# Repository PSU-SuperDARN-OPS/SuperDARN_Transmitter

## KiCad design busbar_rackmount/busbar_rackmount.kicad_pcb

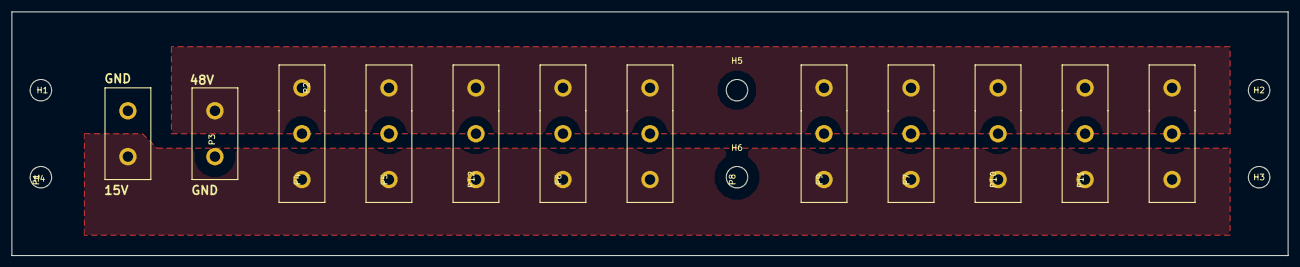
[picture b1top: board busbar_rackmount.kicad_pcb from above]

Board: 2 copper layers, 220.0 x 42.0 mm, 18 parts (0 on the bottom side), 3 nets, no tracks yet.

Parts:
H1, H2, H3, H4, H5, H6: MOUNTING_HOLE; MountingHole_3-7mm
P1, P2: CONN_01X02; powerpole25APCBx2
P3, P4, P5, P6, P7, P8, P9, P10, P11, P12: CONN_01X03; powerpole25APCBx3

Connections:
+15V: P1.1, P3.1, P4.1, P5.1, P6.1, P7.1, P8.1, P9.1, P10.1, P11.1, P12.1
+48V: P2.1, P3.3, P4.3, P5.3, P6.3, P7.3, P8.3, P9.3, P10.3, P11.3, P12.3
GND: P1.2, P2.2, P3.2, P4.2, P5.2, P6.2, P7.2, P8.2, P9.2, P10.2, P11.2, P12.2

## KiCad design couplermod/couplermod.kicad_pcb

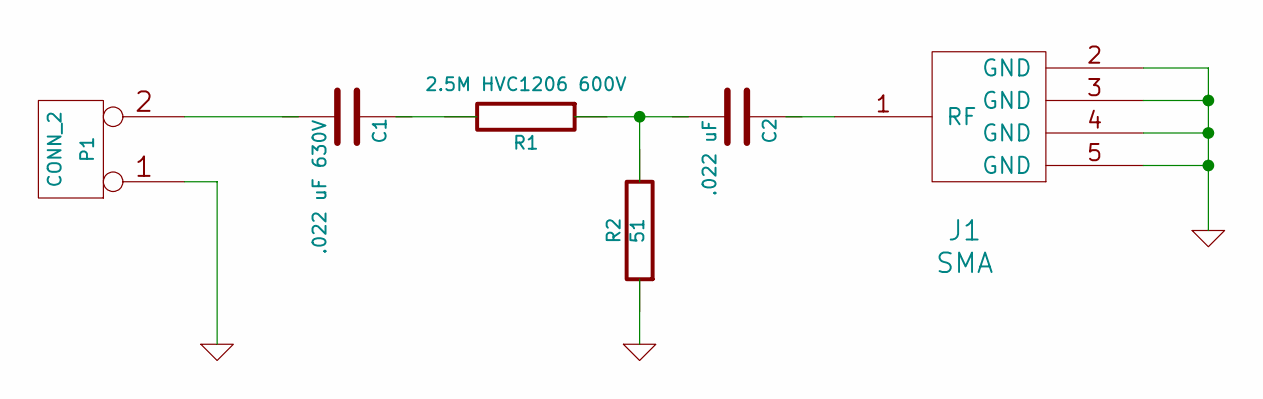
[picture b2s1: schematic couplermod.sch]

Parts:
C1: .022 uF 630V; SMD-1210
C2: .022 uF; SMD-1210
J1: SMA; sma
P1: CONN_2; SIL-2
R1: 2.5M HVC1206 600V; SMD-1210
R2: 51; SMD-0805

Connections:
GND: J1.2 (GND), J1.3 (GND), J1.4 (GND), J1.5 (GND), P1.1, R2.1
unnamed: C1.1, R1.2
unnamed: C1.2, P1.2 (PM)
unnamed: C2.1, J1.1 (RF)
unnamed: C2.2, R1.1, R2.2

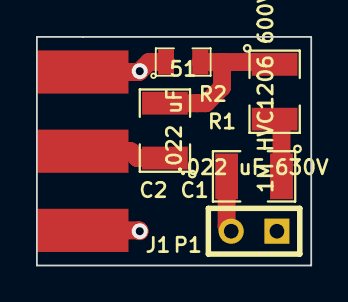
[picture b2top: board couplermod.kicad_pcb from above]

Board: 2 copper layers, 15.2 x 12.7 mm, 6 parts (0 on the bottom side), 5 nets.

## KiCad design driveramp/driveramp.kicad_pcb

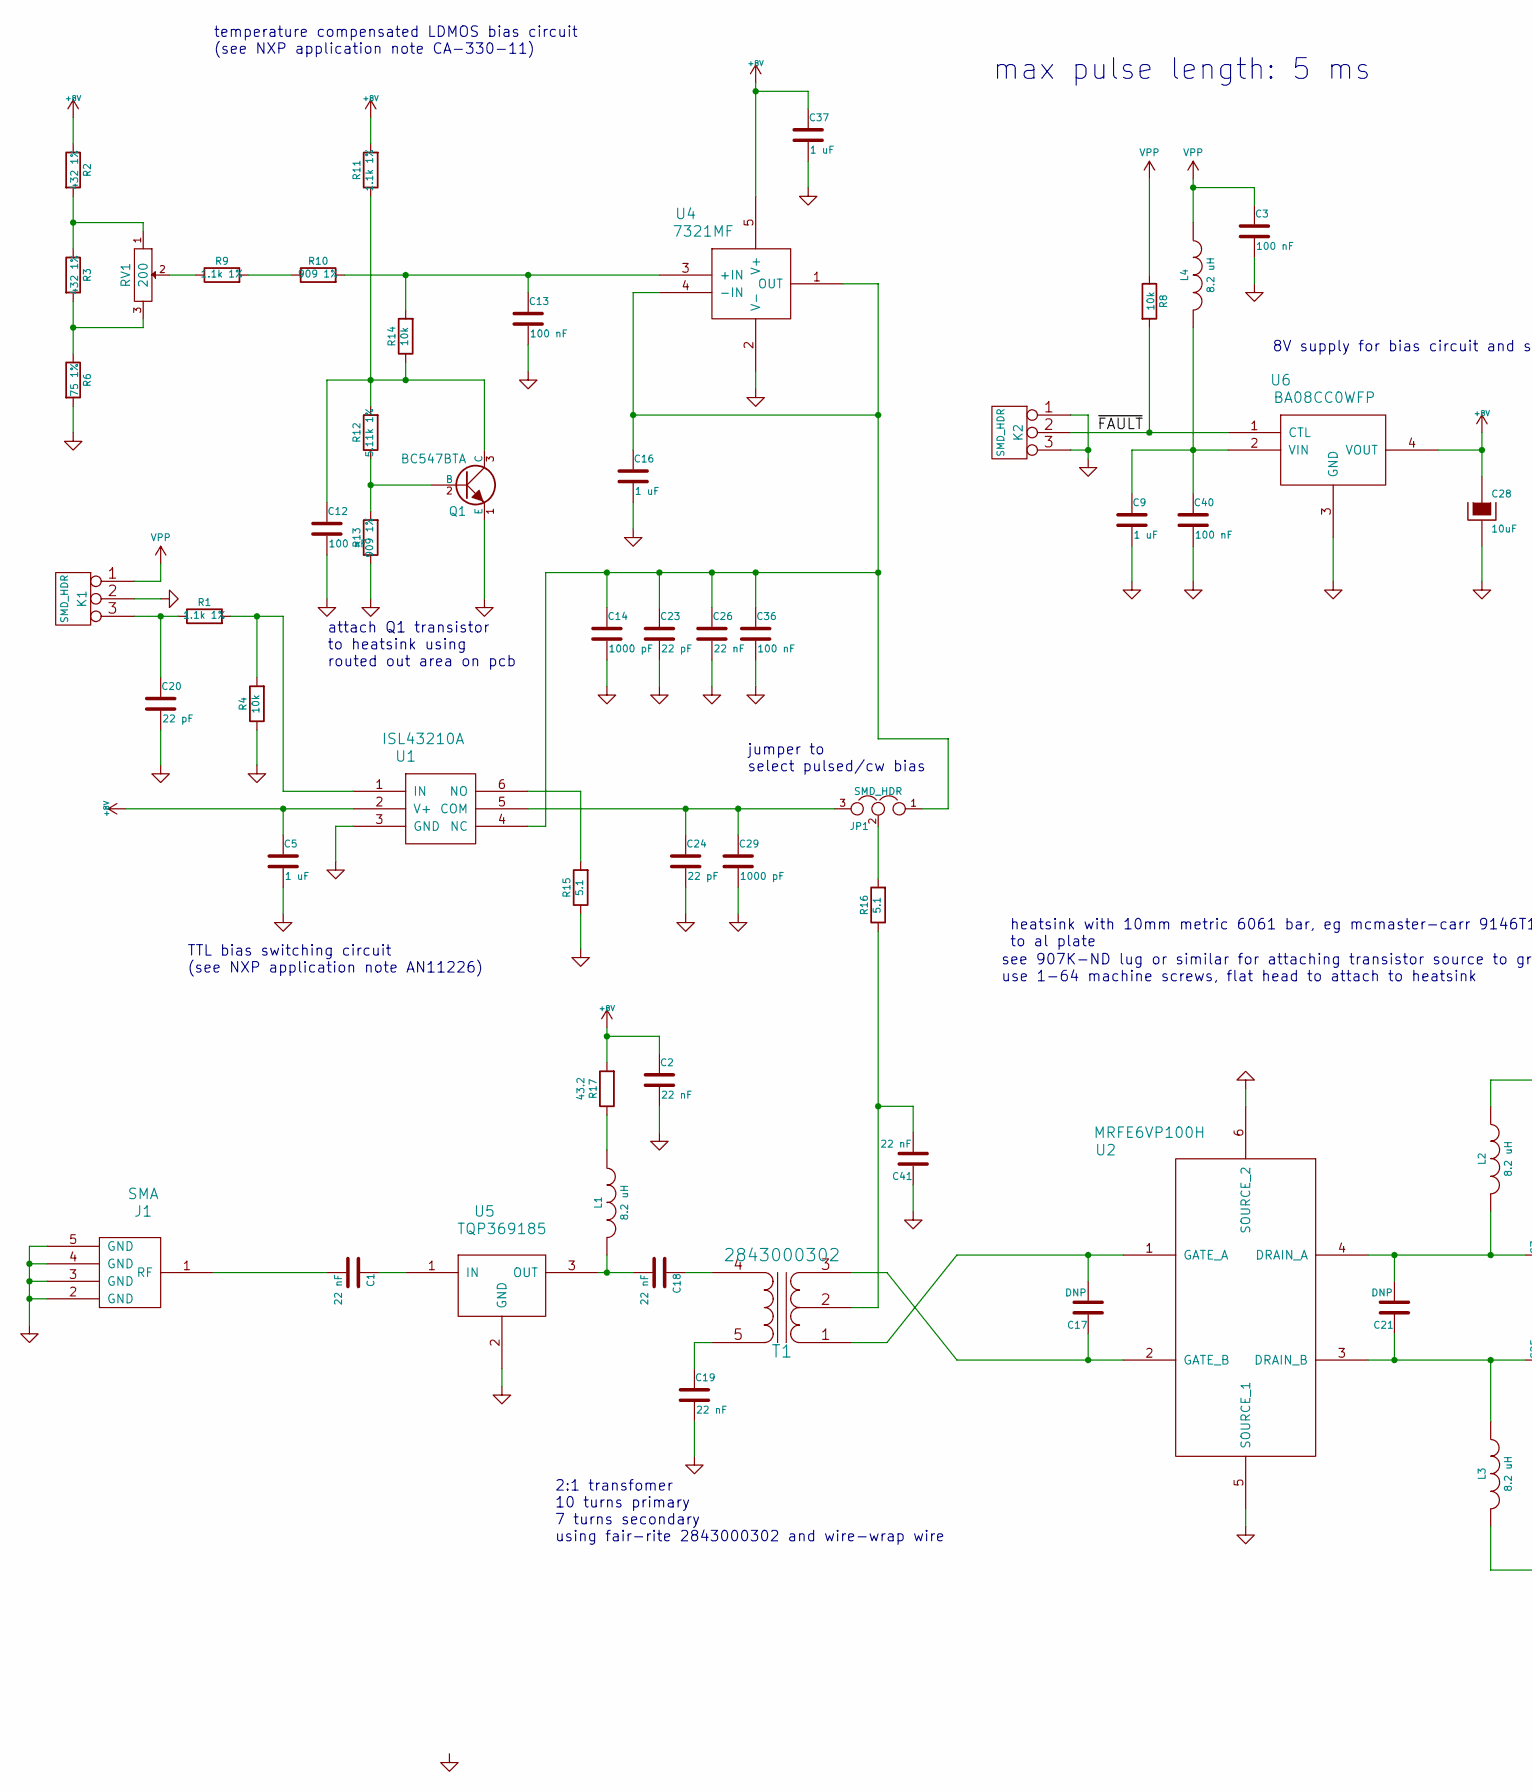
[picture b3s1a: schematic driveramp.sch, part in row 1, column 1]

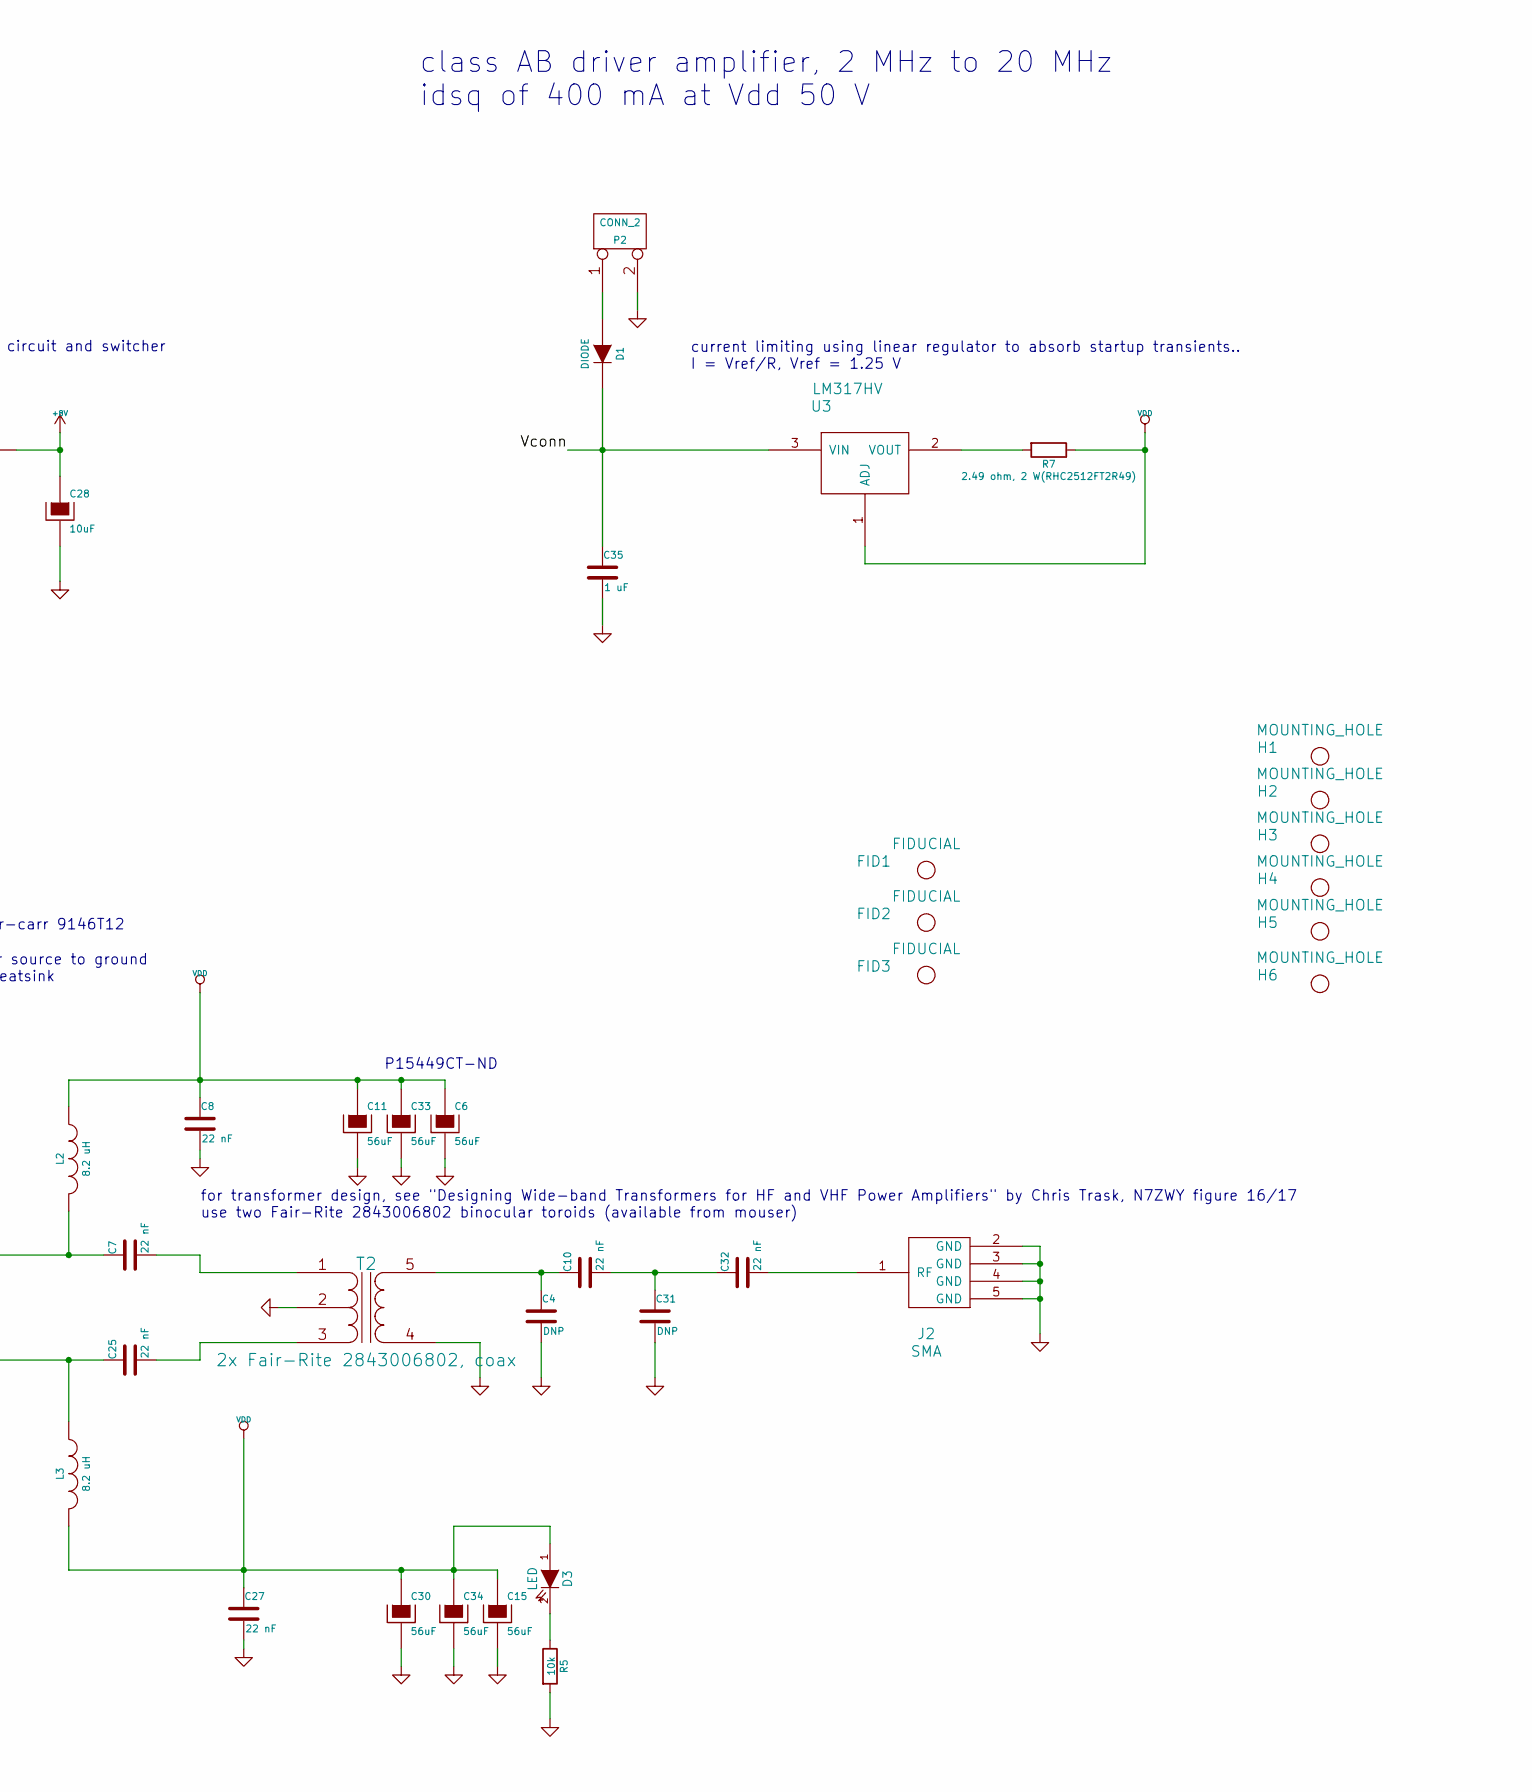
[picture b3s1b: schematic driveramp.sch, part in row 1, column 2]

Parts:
C1, C2, C7, C8, C10, C18, C19, C25, C26, C27, C32, C41: 22 nF; SMD-0805; MFG PN GRM21BR72A223KA01L
C3, C12, C13, C36, C40: 100 nF; SMD-0805; MFG PN CL21B104KCC5PNC
C4, C31: DNP; SMD-1210
C5, C9, C16, C35, C37: 1 uF; C_0805; MFG PN CGA4J3X7S2A105K125AE
C6, C11, C15, C30, C33, C34: 56uF; c_elec_10x10; MFG PN EEH-ZA1J560P
C14, C29: 1000 pF; SMD-0805; MFG PN GRM2195C2A102JA01D
C17, C21: DNP; SMD-0805
C20, C23, C24: 22 pF; C_0805; MFG PN CL21C220JCANNNC
C28: 10uF; c_1210; MFG PN TAJB106M020RNJ
D1: DIODE; DO-214-AA_SMB; MFG PN ES2B
D3: LED; LED-0805; MFG PN LS R976-NR-1
FID1, FID2, FID3: FIDUCIAL; FID_1MM
H1, H2, H3, H4: MOUNTING_HOLE; MountingHole_3-5mm
H5, H6: MOUNTING_HOLE; MountingHole_2-7mm
J1, J2: SMA; SMA_0732511350; MFG PN 732511350
JP1: SMD_HDR; 0740991003
K1, K2: SMD_HDR; 0740991003; MFG PN 740991003
L1, L2, L3, L4: 8.2 uH; Choke_SMD_Wuerth-WE-PD2-Typ-L; MFG PN 7447786008
P2: CONN_2; 2-1445053-2; MFG PN 2-1445096-2
Q1: BC547BTA; TO92SMDSENSE; MFG PN BC547BTA
R1, R9, R11: 1.1k 1%; R_0603; MFG PN ERJ-3EKF1101V
R2, R3: 432 1%; R_0603; MFG PN ERJ-3EKF4320V
R4, R5, R8, R14: 10k; R_0603; MFG PN ERJ-3EKF1002V
R6: 75 1%; R_0603; MFG PN ERJ-3EKF75R0V
R7: 2.49 ohm, 2 W(RHC2512FT2R49); SM2512; MFG PN RHC2512FT2R49
R10, R13: 909 1%; R_0603; MFG PN ERJ-3EKF9090V
R12: 5.11k 1%; R_0603; MFG PN ERJ-3EKF5111V
R15, R16: 5.1; R_0603; MFG PN ERJ-3EKF5111V
R17: 43.2; SMD-2512_Pol; MFG PN MCR100JZHF43R2
RV1: 200; 3269W; MFG PN 3269W-1-201GLF
T1: 2843000302; MFG PN 2843000302
T2: 2x Fair-Rite 2843006802, coax; 2843006802; MFG PN 2843006802
U1: ISL43210A; SOT-23-6; MFG PN ISL43210AIHZ-T7A
U2: MRFE6VP100H; NI780-4; MFG PN MRFE6VP100HR5
U3: LM317HV; TO-220_Neutral123_Horizontal; MFG PN LM317HVT/NOPB
U4: 7321MF; SOT-23-5; MFG PN LM7321MF/NOPB
U5: TQP369185; SOT89-3_Housing; MFG PN TQP369185
U6: BA08CC0WFP; TO252-5; MFG PN BA08CC0WFP-E2

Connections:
+8V: C2.1, C5.1, C28.1, C37.1, R2.1, R11.2, R17.2, U1.2 (V+), U4.5 (V+), U6.4 (VOUT)
/Vconn: C35.1, D1.2 (K), U3.3 (VIN)
/~FAULT: K2.2 (PM), R8.2, U6.1 (CTL)
GND: C2.2, C3.2, C4.2, C5.2, C6.2, C8.2, C9.2, C11.2, C12.2, C13.2, C14.2, C15.2, C16.2, C19.2, C20.2, C23.2, C24.2, C26.2, C27.2, C28.2, C29.2, C30.2, C31.2, C33.2, C34.2, C35.2, C36.2, C37.2, C40.2, C41.1, J1.2 (GND), J1.3 (GND), J1.4 (GND), J1.5 (GND), J2.2 (GND), J2.3 (GND), J2.4 (GND), J2.5 (GND), K1.2 (PM), K2.1, K2.3, P2.2 (PM), Q1.1 (E), R4.1, R5.2, R6.2, R13.1, R15.1, T2.2 (PM), T2.4 (S1), U1.3 (GND), U2.5 (SOURCE_1), U2.6 (SOURCE_2), U4.2 (V-), U5.2 (GND), U6.3 (GND)
unnamed: C1.1, U5.1 (IN)
unnamed: C1.2, J1.1 (RF)
unnamed: C7.2, T2.1 (PR1)
unnamed: C4.1, C10.1, T2.5 (S2)
unnamed: C10.2, C31.1, C32.1
unnamed: C12.1, Q1.3 (C), R11.1, R12.2, R14.1
unnamed: C13.1, R10.2, R14.2, U4.3 (+IN)
unnamed: C14.1, C16.1, C23.1, C26.1, C36.1, JP1.1, U1.4 (NC), U4.1 (OUT), U4.4 (-IN)
unnamed: C17.1, T1.3 (PR2), U2.2 (GATE_B)
unnamed: C17.2, T1.1 (PR1), U2.1 (GATE_A)
unnamed: C18.1, T1.4 (S1)
unnamed: C18.2, L1.2, U5.3 (OUT)
unnamed: C19.1, T1.5 (S2)
unnamed: C20.1, K1.3, R1.1
unnamed: C21.1, C25.1, L3.1, U2.3 (DRAIN_B)
unnamed: C7.1, C21.2, L2.2, U2.4 (DRAIN_A)
unnamed: C24.1, C29.1, JP1.3, U1.5 (COM)
unnamed: C25.2, T2.3 (PR2)
unnamed: C32.2, J2.1 (RF)
unnamed: C9.1, C40.1, L4.2, U6.2 (VIN)
unnamed: C41.2, R16.1, T1.2 (PM)
unnamed: D1.1 (A), P2.1
unnamed: D3.2 (K), R5.1
unnamed: JP1.2, R16.2
unnamed: L1.1, R17.1
unnamed: Q1.2 (B), R12.1, R13.2
unnamed: R1.2, R4.2, U1.1 (IN)
unnamed: R2.2, R3.1, RV1.1
unnamed: R3.2, R6.1, RV1.3
unnamed: R7.2, U3.2 (VOUT)
unnamed: R9.1, RV1.2
unnamed: R9.2, R10.1
unnamed: R15.2, U1.6 (NO)
VDD: C6.1, C8.1, C11.1, C15.1, C27.1, C30.1, C33.1, C34.1, D3.1 (A), L2.1, L3.2, R7.1, U3.1 (ADJ)
VPP: C3.1, K1.1, L4.1, R8.1

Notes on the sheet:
class AB driver amplifier, 2 MHz to 20 MHz idsq of 400 mA at Vdd 50 V
P15449CT-ND
for transformer design, see "Designing Wide-band Transformers for HF and VHF Power Amplifiers" by Chris Trask, N7ZWY figure 16/17 use two Fair-Rite 2843006802 binocular toroids (available from mouser)
current limiting using linear regulator to absorb startup transients.. I = Vref/R, Vref = 1.25 V
max pulse length: 5 ms
see 907K-ND lug or similar for attaching transistor source to ground use 1-64 machine screws, flat head to attach to heatsink
temperature compensated LDMOS bias circuit (see NXP application note CA-330-11)
TTL bias switching circuit (see NXP application note AN11226)
8V supply for bias circuit and switcher
heatsink with 10mm metric 6061 bar, eg mcmaster-carr 9146T12 to al plate
attach Q1 transistor to heatsink using routed out area on pcb
jumper to select pulsed/cw bias
2:1 transfomer 10 turns primary 7 turns secondary using fair-rite 2843000302 and wire-wrap wire

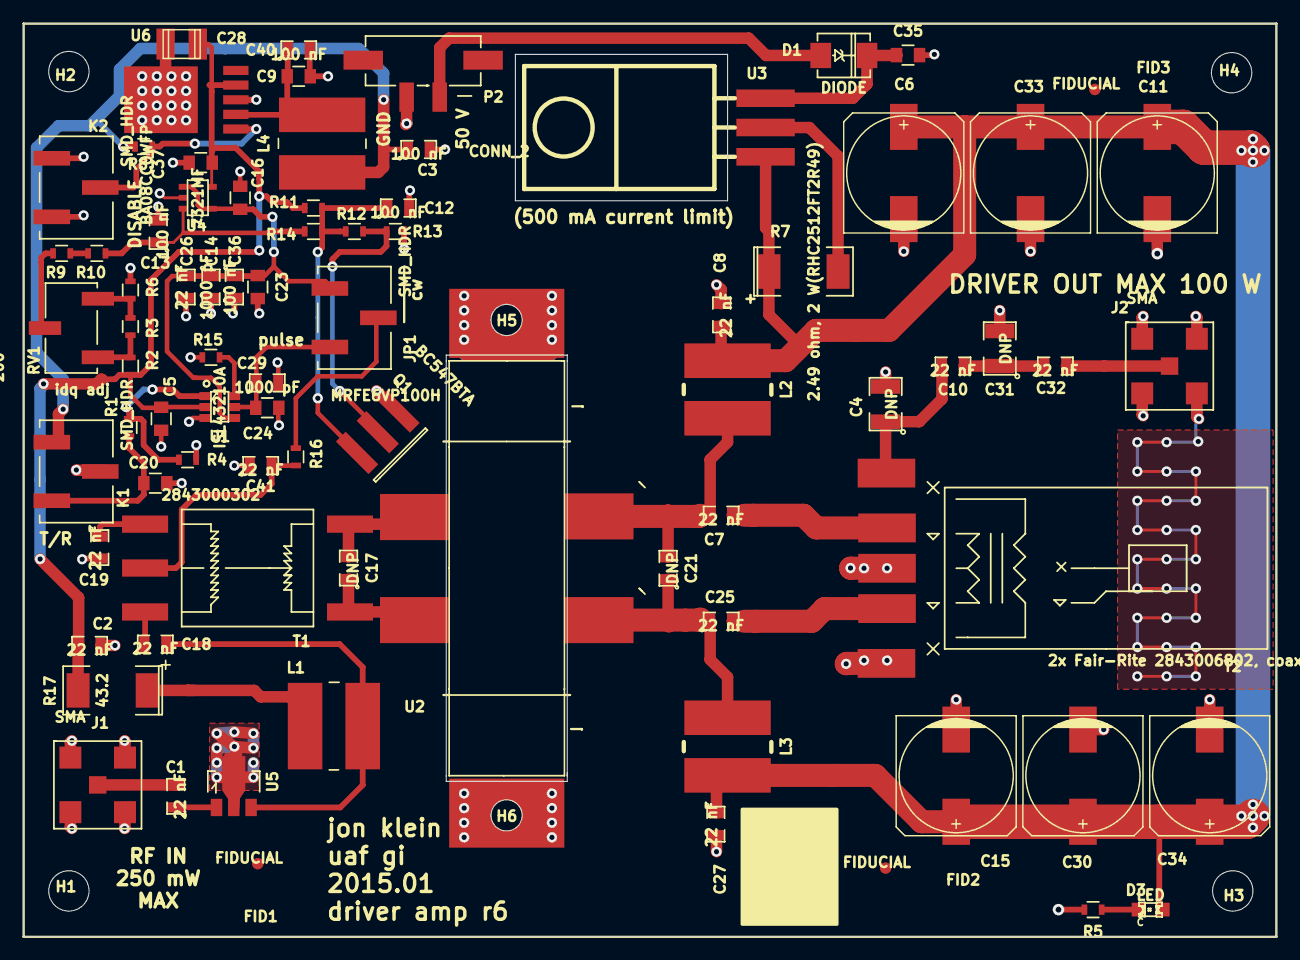
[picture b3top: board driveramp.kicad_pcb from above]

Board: 2 copper layers, 108.7 x 79.2 mm, 86 parts (0 on the bottom side), 39 nets.

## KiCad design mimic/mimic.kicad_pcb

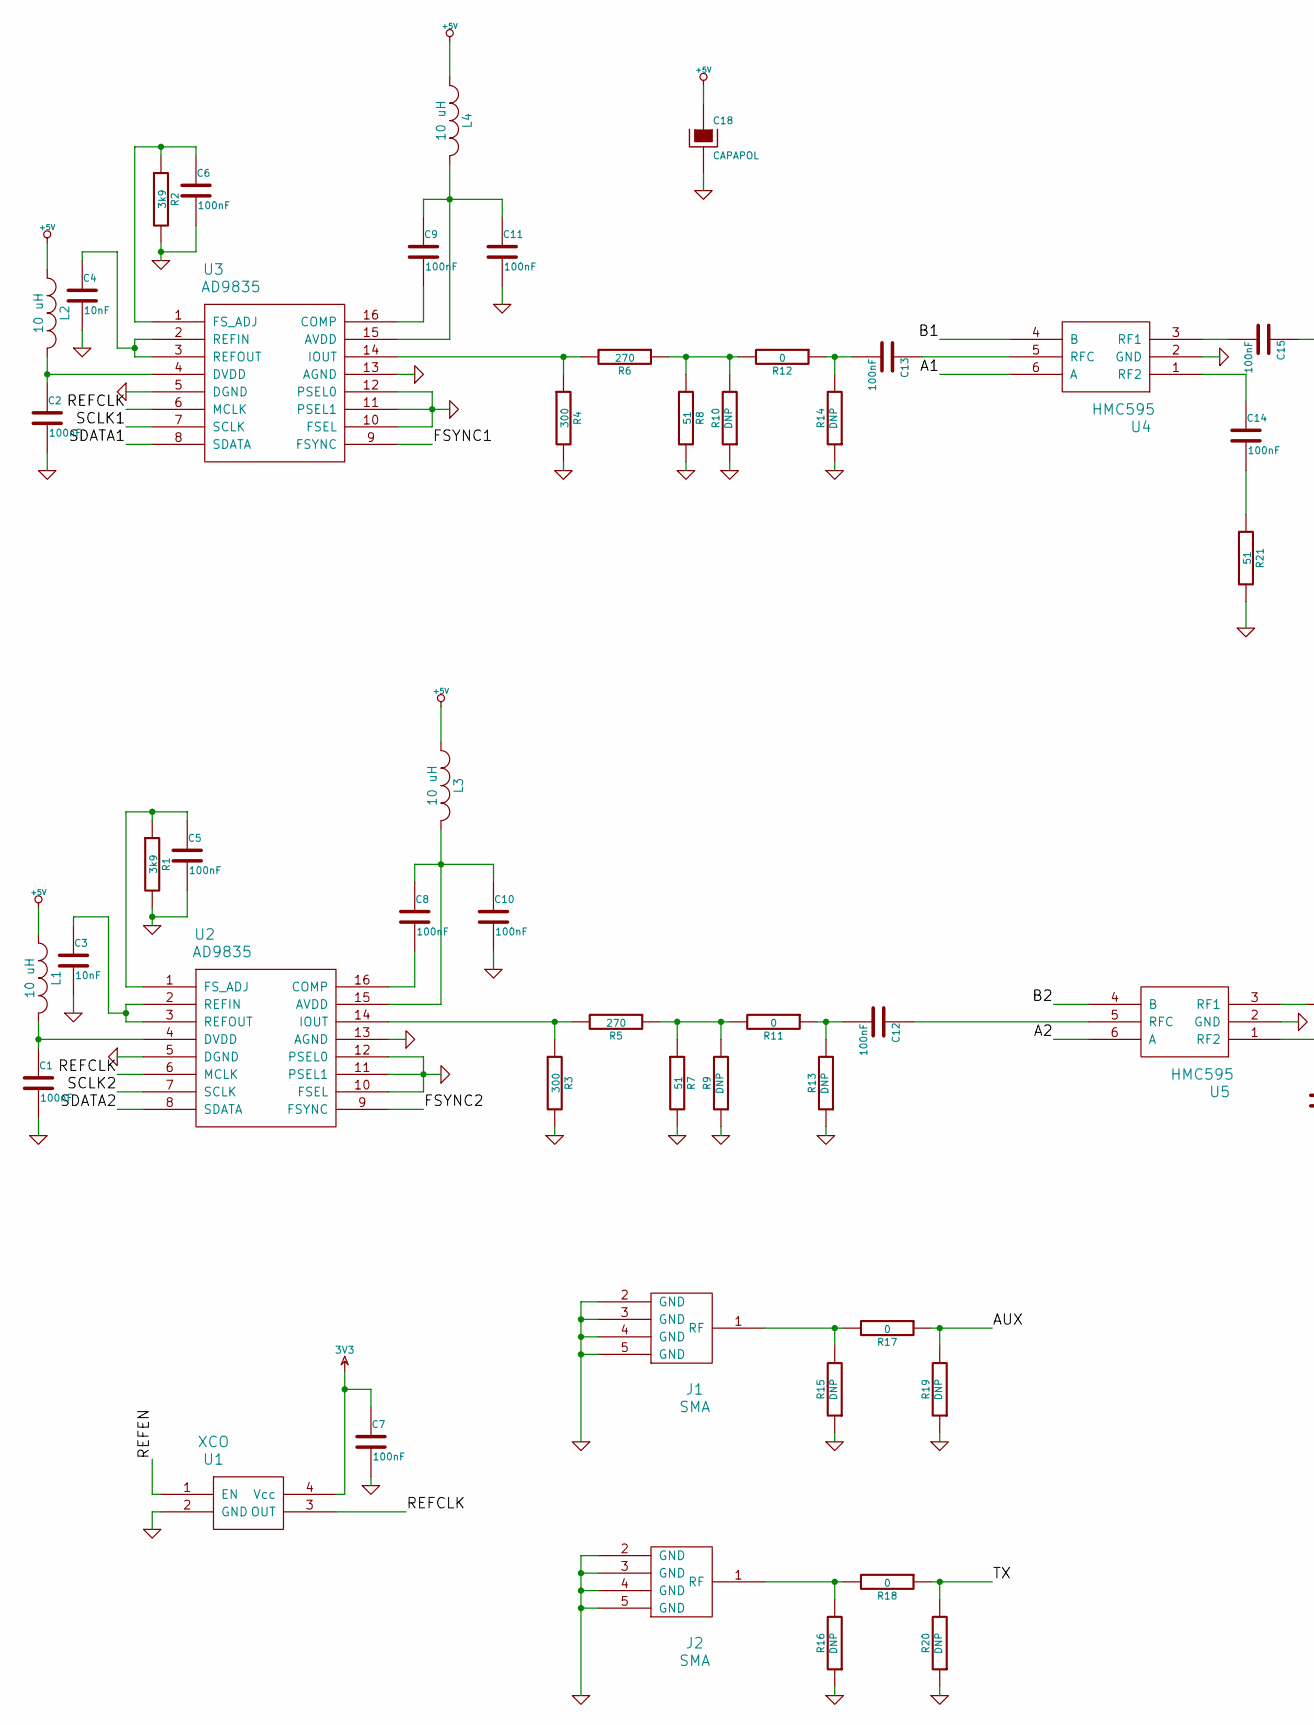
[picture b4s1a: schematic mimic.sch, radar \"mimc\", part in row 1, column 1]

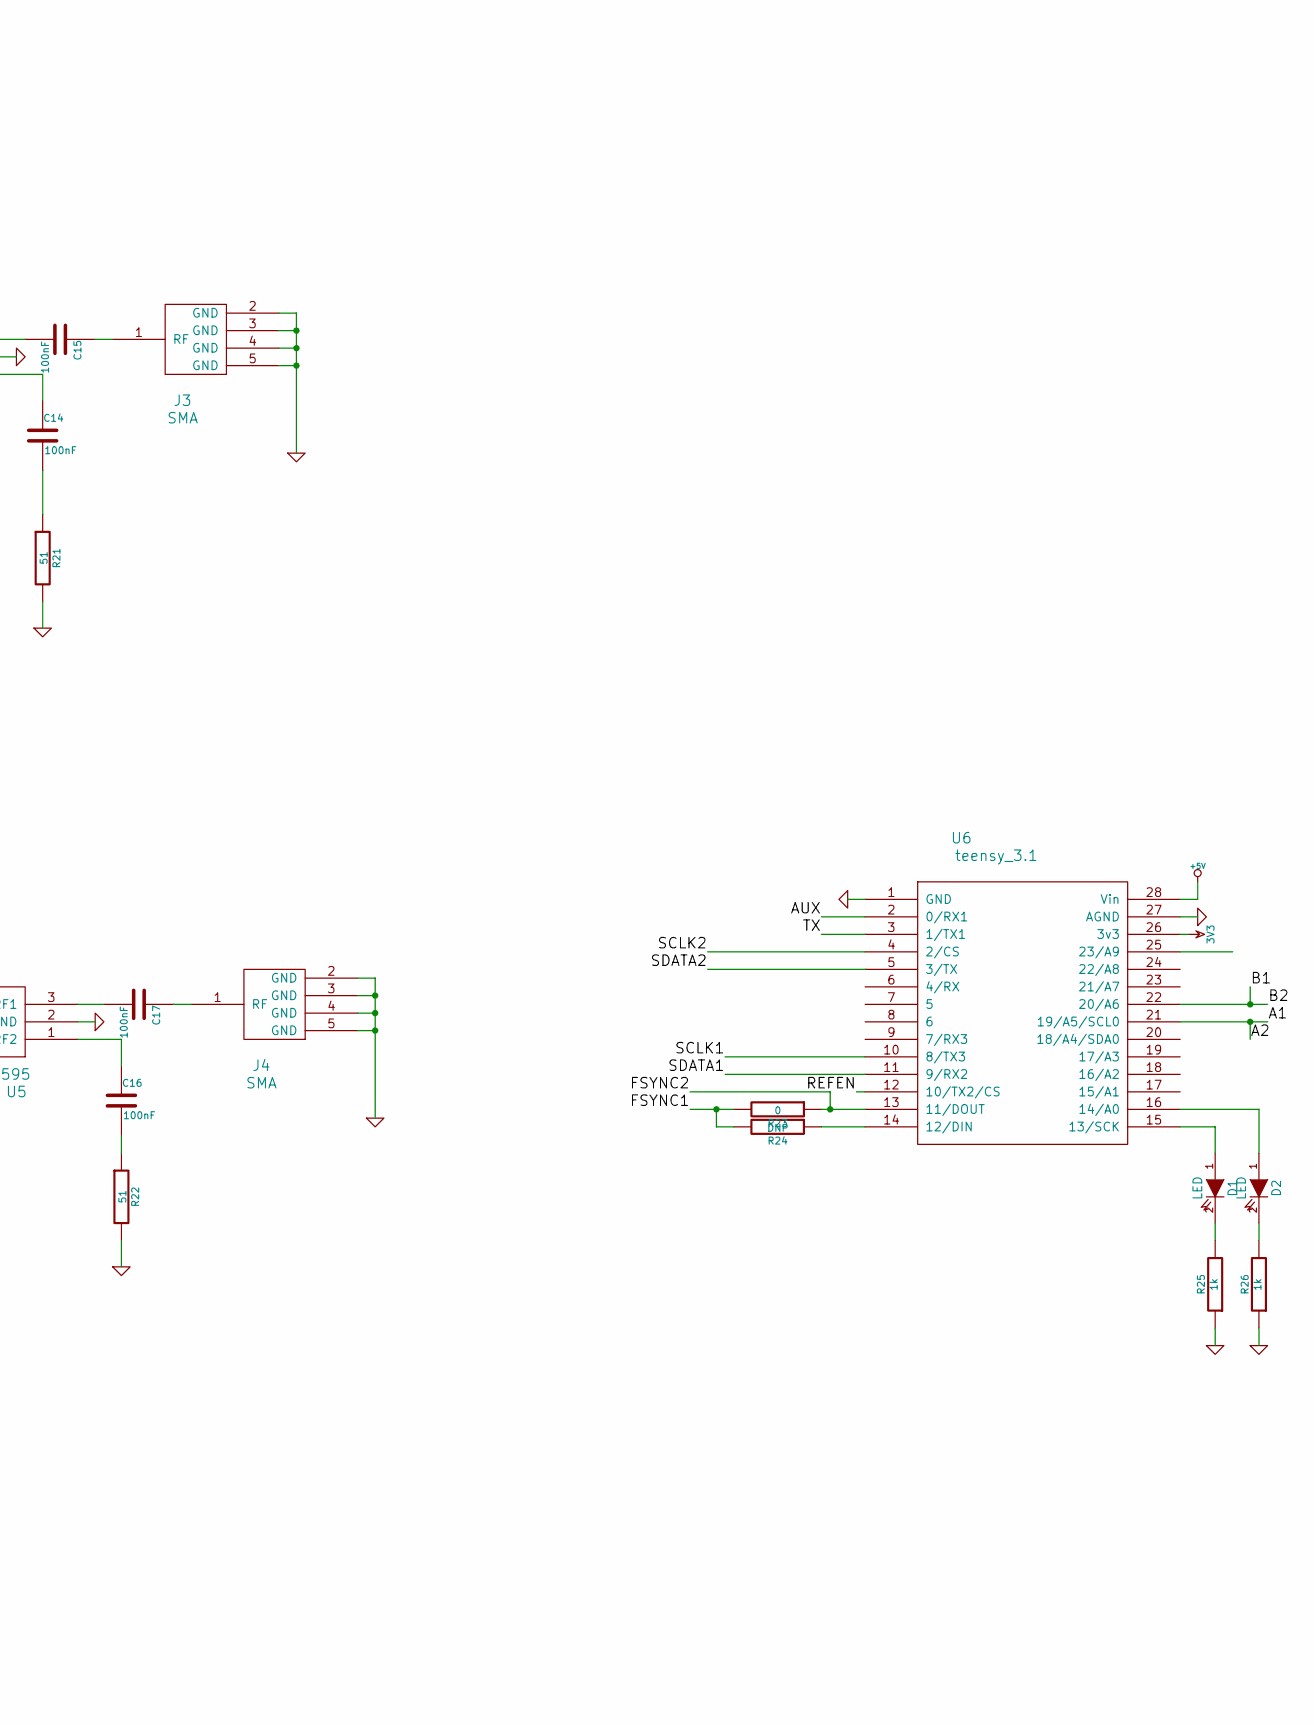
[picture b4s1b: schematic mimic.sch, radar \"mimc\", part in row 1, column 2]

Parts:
C1, C2, C5, C6, C7, C8, C9, C10, C11, C12, C13, C14, C15, C16, C17: 100nF; SM0603
C3, C4: 10nF; SM0603
C18: CAPAPOL; SM1210
D1, D2: LED; SM0603
J1, J2, J3, J4: SMA; sma
L1, L2, L3, L4: 10 uH; SM1210
R1, R2: 3k9; SM0603
R3, R4: 300; SM0603
R5, R6: 270; SM0603
R7, R8, R21, R22: 51; SM0603
R9, R10, R13, R14, R15, R16, R19, R20, R24: DNP; SM0603
R11, R12, R17, R18, R23: 0; SM0603
R25, R26: 1k; SM0603
U1: XCO; crystal_FA238-TSX3225
U2, U3: AD9835; TSSOP16
U4, U5: HMC595; SOT23_6
U6: teensy_3.1; DIP-28__600

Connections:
3V3: C7.1, U1.4 (Vcc), U6.26 (3v3)
+5V: C18.1, L1.1, L2.1, L3.1, L4.1, U6.28 (Vin)
/A1: U4.6 (A), U5.6 (A), U6.21 (19/A5/SCL0)
/AUX: R17.1, R19.2, U6.2 (0/RX1)
/B1: U4.4 (B), U5.4 (B), U6.22 (20/A6)
/FSYNC1: R23.2, R24.2, U3.9 (FSYNC)
/FSYNC2: R23.1, U2.9 (FSYNC), U6.13 (11/DOUT)
/REFCLK: U1.3 (OUT), U2.6 (MCLK), U3.6 (MCLK)
/REFEN: U1.1 (EN), U6.12 (10/TX2/CS)
/SCLK1: U3.7 (SCLK), U6.10 (8/TX3)
/SCLK2: U2.7 (SCLK), U6.4 (2/CS)
/SDATA1: U3.8 (SDATA), U6.11 (9/RX2)
/SDATA2: U2.8 (SDATA), U6.5 (3/TX)
/TX: R18.1, R20.2, U6.3 (1/TX1)
GND: C1.2, C2.2, C3.2, C4.2, C5.2, C6.2, C7.2, C10.2, C11.2, C18.2, J1.2 (GND), J1.3 (GND), J1.4 (GND), J1.5 (GND), J2.2 (GND), J2.3 (GND), J2.4 (GND), J2.5 (GND), J3.2 (GND), J3.3 (GND), J3.4 (GND), J3.5 (GND), J4.2 (GND), J4.3 (GND), J4.4 (GND), J4.5 (GND), R1.2, R2.2, R3.2, R4.2, R7.2, R8.2, R9.1, R10.1, R13.1, R14.1, R15.1, R16.1, R19.1, R20.1, R21.2, R22.2, R25.1, R26.1, U1.2 (GND), U2.5 (DGND), U2.10 (FSEL), U2.11 (PSEL1), U2.12 (PSEL0), U2.13 (AGND), U3.5 (DGND), U3.10 (FSEL), U3.11 (PSEL1), U3.12 (PSEL0), U3.13 (AGND), U4.2 (GND), U5.2 (GND), U6.1 (GND), U6.27 (AGND)
unnamed: C1.1, L1.2, U2.4 (DVDD)
unnamed: C2.1, L2.2, U3.4 (DVDD)
unnamed: C3.1, U2.2 (REFIN), U2.3 (REFOUT)
unnamed: C4.1, U3.2 (REFIN), U3.3 (REFOUT)
unnamed: C5.1, R1.1, U2.1 (FS_ADJ)
unnamed: C6.1, R2.1, U3.1 (FS_ADJ)
unnamed: C8.2, U2.16 (COMP)
unnamed: C9.2, U3.16 (COMP)
unnamed: C8.1, C10.1, L3.2, U2.15 (AVDD)
unnamed: C9.1, C11.1, L4.2, U3.15 (AVDD)
unnamed: C12.1, U5.5 (RFC)
unnamed: C12.2, R11.1, R13.2
unnamed: C13.1, U4.5 (RFC)
unnamed: C13.2, R12.1, R14.2
unnamed: C14.1, U4.1 (RF2)
unnamed: C14.2, R21.1
unnamed: C15.1, J3.1 (RF)
unnamed: C15.2, U4.3 (RF1)
unnamed: C16.1, U5.1 (RF2)
unnamed: C16.2, R22.1
unnamed: C17.1, J4.1 (RF)
unnamed: C17.2, U5.3 (RF1)
unnamed: D1.1 (A), U6.15 (13/SCK)
unnamed: D1.2 (K), R25.2
unnamed: D2.1 (A), U6.16 (14/A0)
unnamed: D2.2 (K), R26.2
unnamed: J1.1 (RF), R15.2, R17.2
unnamed: J2.1 (RF), R16.2, R18.2
unnamed: R3.1, R5.2, U2.14 (IOUT)
unnamed: R4.1, R6.2, U3.14 (IOUT)
unnamed: R6.1, R8.1, R10.2, R12.2
unnamed: R5.1, R7.1, R9.2, R11.2
unnamed: R24.1, U6.14 (12/DIN)

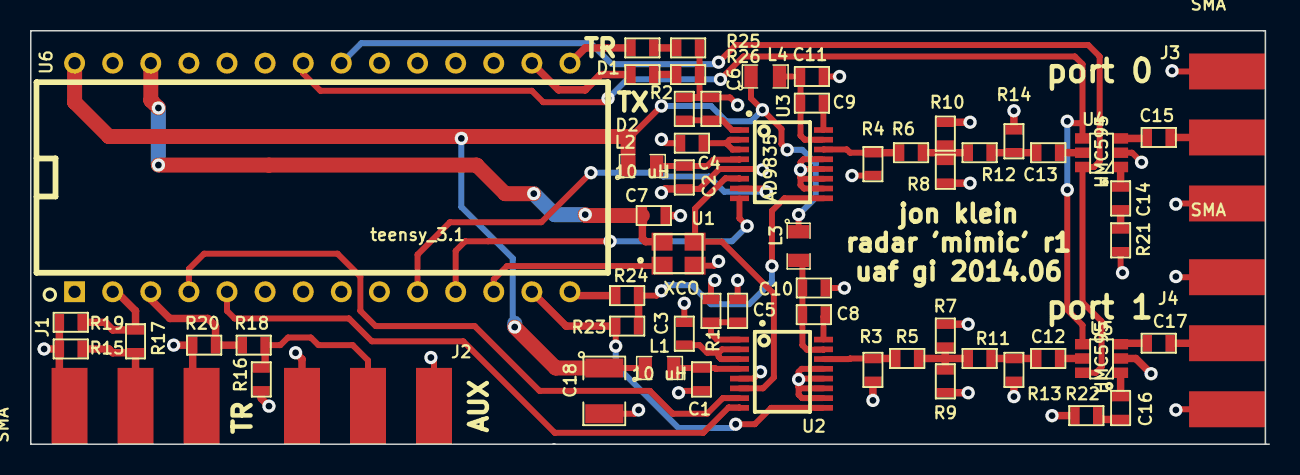
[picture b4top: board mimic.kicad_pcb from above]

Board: 2 copper layers, 82.6 x 27.6 mm, 60 parts (0 on the bottom side), 48 nets.

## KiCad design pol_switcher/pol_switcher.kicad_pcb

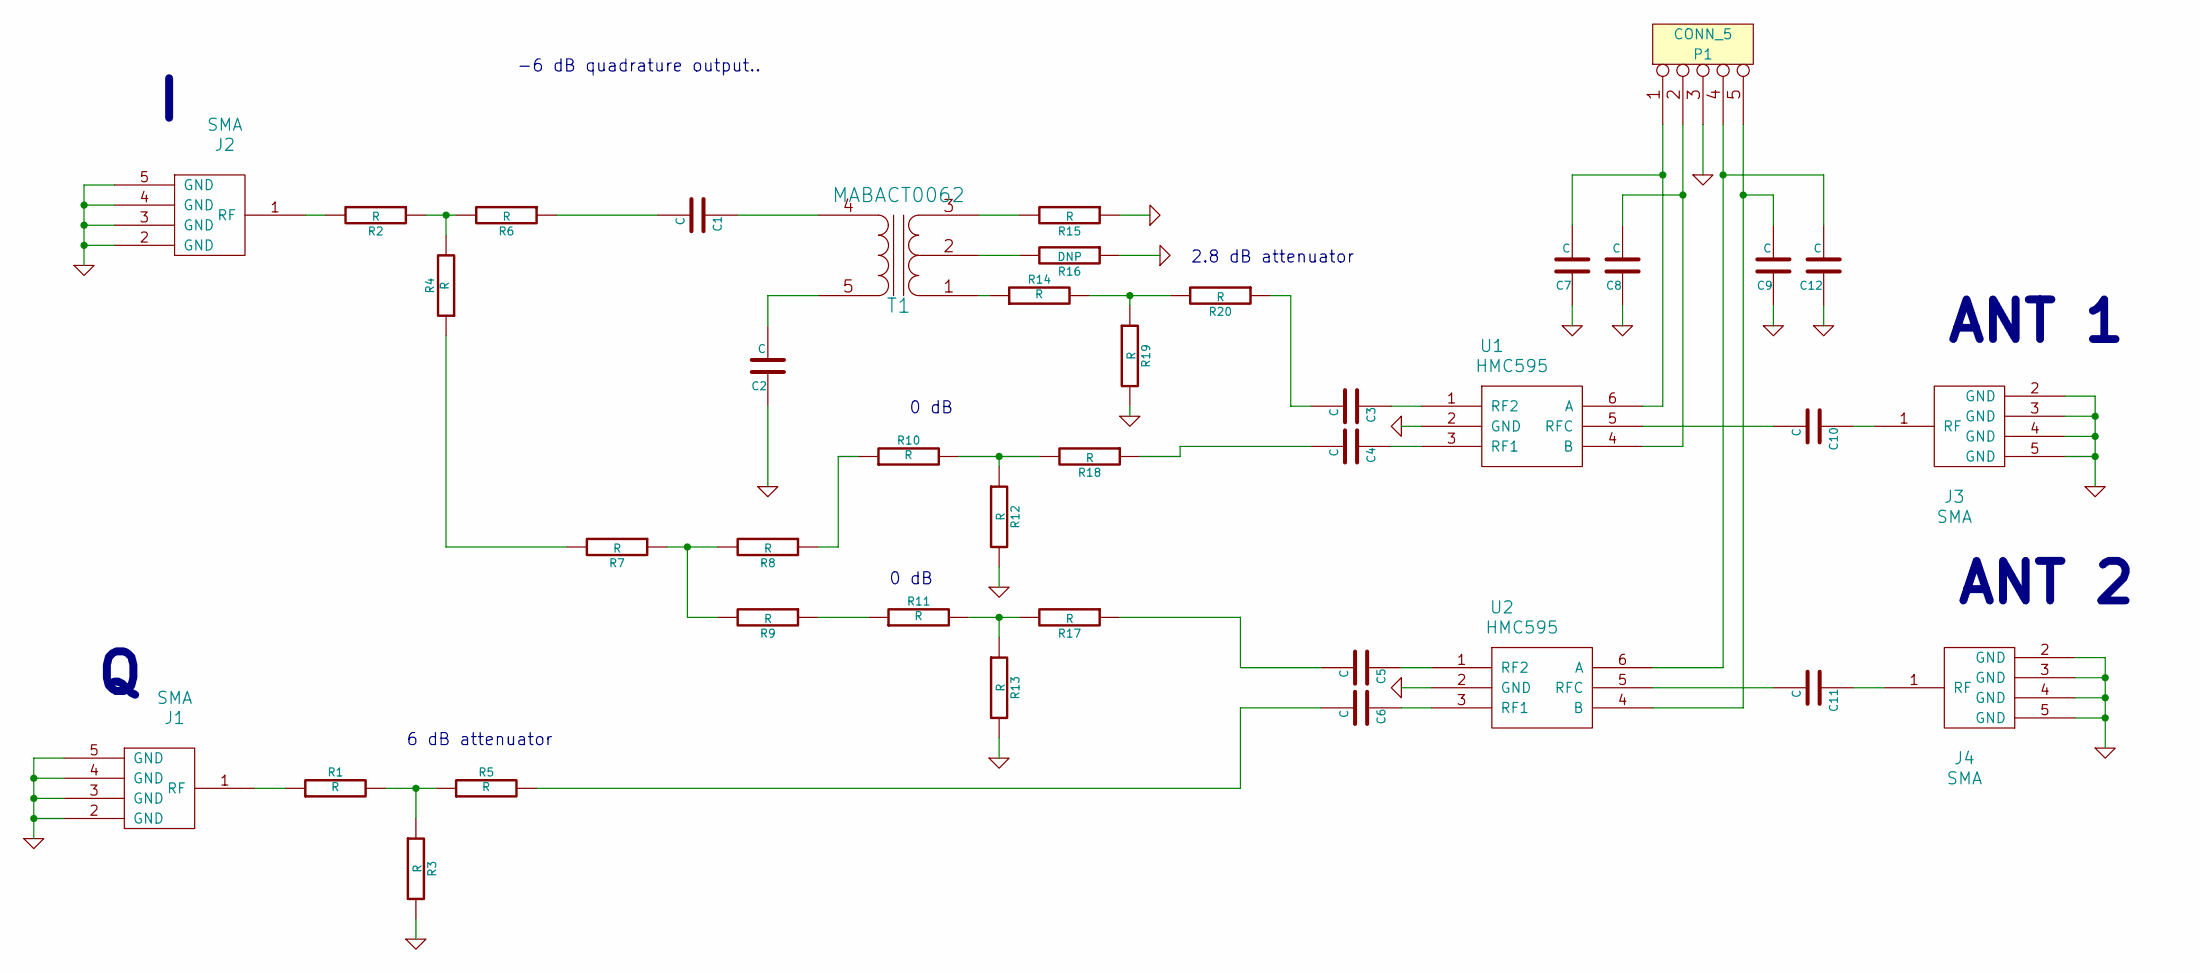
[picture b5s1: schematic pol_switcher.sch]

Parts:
C1, C2, C3, C4, C5, C6, C7, C8, C9, C10, C11, C12: C
J1, J2, J3, J4: SMA
P1: CONN_5
R1, R2, R3, R4, R5, R6, R7, R8, R9, R10, R11, R12, R13, R14, R15, R17, R18, R19, R20: R
R16: DNP
T1: MABACT0062
U1, U2: HMC595

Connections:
GND: C2.1, C7.1, C8.1, C9.1, C12.1, J1.2 (GND), J1.3 (GND), J1.4 (GND), J1.5 (GND), J2.2 (GND), J2.3 (GND), J2.4 (GND), J2.5 (GND), J3.2 (GND), J3.3 (GND), J3.4 (GND), J3.5 (GND), J4.2 (GND), J4.3 (GND), J4.4 (GND), J4.5 (GND), P1.3, R3.2, R12.2, R13.2, R15.1, R16.1, R19.2, U1.2 (GND), U2.2 (GND)
unnamed: C1.1, T1.4 (S1)
unnamed: C1.2, R6.1
unnamed: C2.2, T1.5 (S2)
unnamed: C3.1, U1.1 (RF2)
unnamed: C3.2, R20.1
unnamed: C4.1, U1.3 (RF1)
unnamed: C4.2, R18.1
unnamed: C5.1, U2.1 (RF2)
unnamed: C5.2, R17.1
unnamed: C6.1, U2.3 (RF1)
unnamed: C6.2, R5.2
unnamed: C7.2, P1.1, U1.6 (A)
unnamed: C8.2, P1.2, U1.4 (B)
unnamed: C9.2, P1.5, U2.4 (B)
unnamed: C10.1, J3.1 (RF)
unnamed: C10.2, U1.5 (RFC)
unnamed: C11.1, J4.1 (RF)
unnamed: C11.2, U2.5 (RFC)
unnamed: C12.2, P1.4, U2.6 (A)
unnamed: J1.1 (RF), R1.1
unnamed: J2.1 (RF), R2.2
unnamed: R1.2, R3.1, R5.1
unnamed: R2.1, R4.2, R6.2
unnamed: R4.1, R7.2
unnamed: R7.1, R8.2, R9.2
unnamed: R8.1, R10.1
unnamed: R10.2, R12.1, R18.2
unnamed: R9.1, R11.1
unnamed: R11.2, R13.1, R17.2
unnamed: R14.1, T1.1 (PR1)
unnamed: R14.2, R19.1, R20.2
unnamed: R15.2, T1.3 (PR2)
unnamed: R16.2, T1.2 (PM)

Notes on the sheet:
ANT 1
ANT 2
6 dB attenuator
2.8 dB attenuator
0 dB
-6 dB quadrature output..

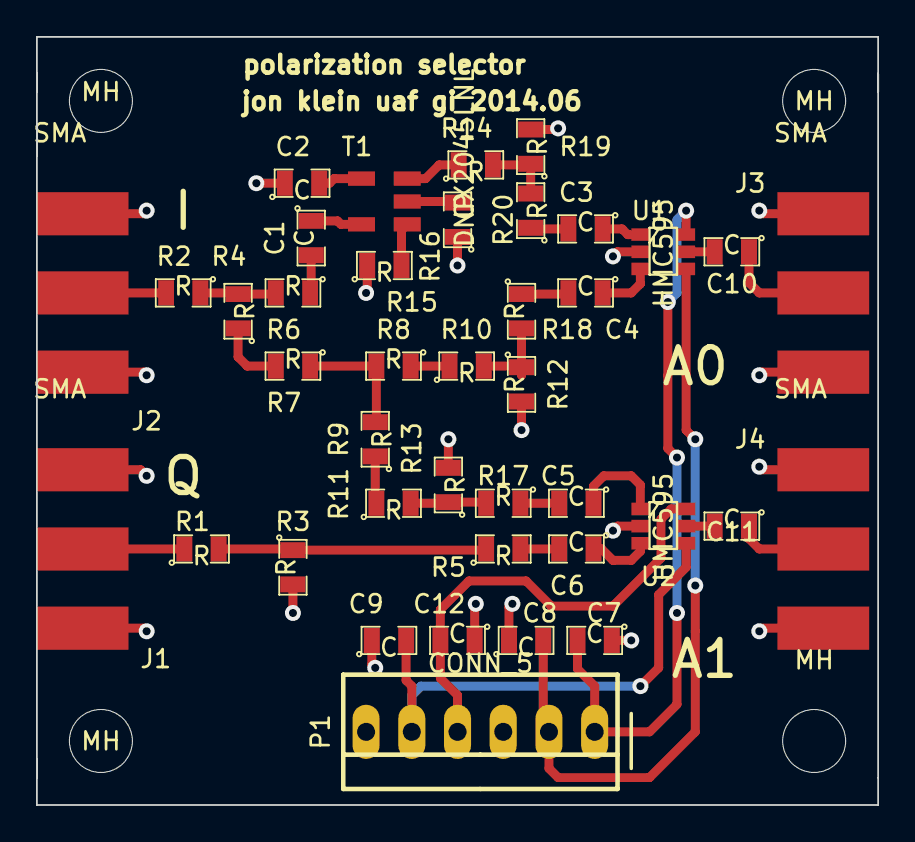
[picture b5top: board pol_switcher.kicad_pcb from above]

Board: 2 copper layers, 46.7 x 42.7 mm, 44 parts (0 on the bottom side), 34 nets.

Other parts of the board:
MH: MountingHole_3-5mm_RevA_Date21Jun2010; MountingHole_3-5mm
MH#2, MH#3, MH#4: MountingHole_3-5mm_RevA_Date21Jun2010; MountingHole_3-5mm
